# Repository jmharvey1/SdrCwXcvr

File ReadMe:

This repository contains files used to build the CW transceiver
shown in the YouTube Video at:
https://youtu.be/vxcRsNkiOTE
Some general instructions on how the files are to be used will be found here as well.
Use "SDR 74HC4052_Si5351R2_2020-03-30.zip" found in the Eagle/SDR 74HC4052 folder, to order a board from a pcb service, like JLCPCB.
Disclaimer: Some folders found here may not be complete. If you think that's preventing you
from being able to use them. Please use the "issues" section or the youtube's comments area 
to describe the problem. Hopefully I will be able to add the missing files.

Note: the "Quisk" folder supports Quisk running on Mint19.1 & Python 2.7. "quiskKW4KDpy3.tar.gz" is for Mint20 / Python 3. To install and run these versions of QUISK, follow the Linux Initial Installation" instuctions found here: 	https://james.ahlstrom.name/quisk/docs.html#Welcome
But use the source files found here, inplace of the onse referenced at the QUISK website

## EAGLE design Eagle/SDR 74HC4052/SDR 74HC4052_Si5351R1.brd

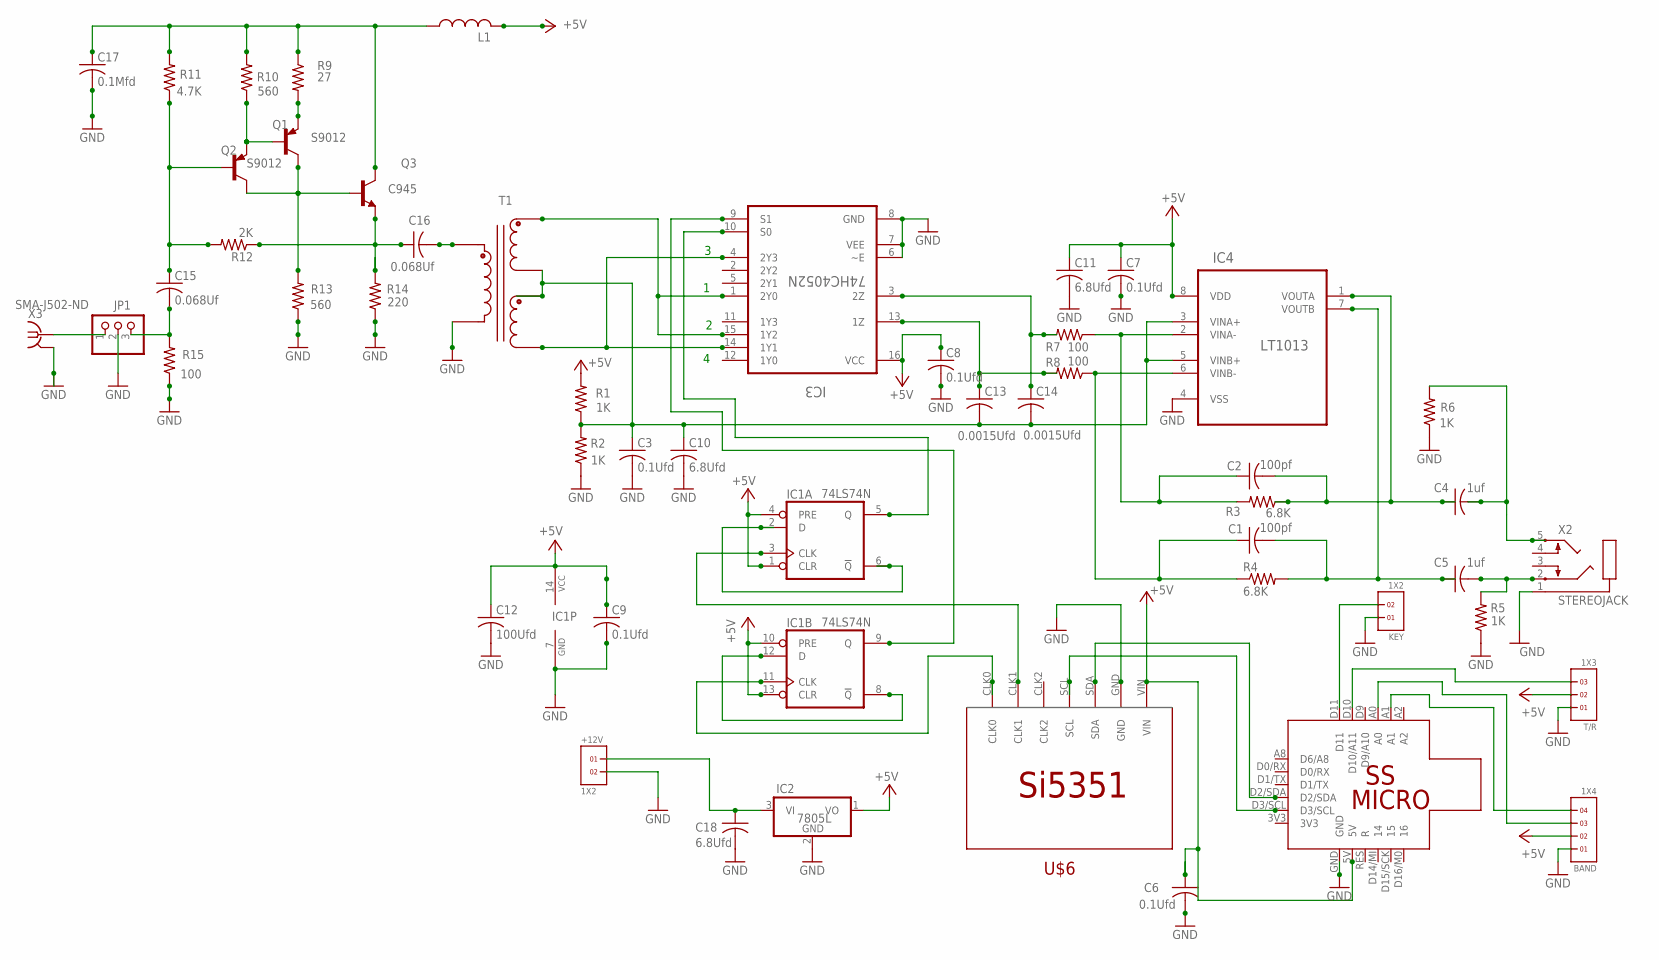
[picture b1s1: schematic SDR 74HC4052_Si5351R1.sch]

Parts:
+12V: 1X2
BAND: 1X4
C1, C2: 100pf; C050-024X044
C3, C6, C7, C8, C9: 0.1Ufd; C050-024X044
C4, C5: 1uf; C050-024X044
C10, C11, C18: 6.8Ufd; C050-024X044
C12: 100Ufd; C050-024X044
C13, C14: 0.0015Ufd; C050-024X044
C15, C16: 0.068Uf; C050-024X044
C17: 0.1Mfd; C050-024X044
IC1: 74LS74N; DIL14
IC2: 7805L; TO92
IC3: 74HC4052N; DIL16
IC4: LT1013; DIP254P762X533-8
JP1: PINHD-1X3CB; 1X03-CLEANBIG
KEY: 1X2
L1: L-US0207/12; 0207/12
Q1, Q2: S9012; TO92-CBE
Q3: C945; TO92-ECB
R1, R2, R5, R6: 1K; 0207/10
R3, R4: 6.8K; 0207/10
R7, R8: 100; 0207/10
R9: 27; 0207/7
R10, R13: 560; 0207/7
R11: 4.7K; 0207/7
R12: 2K; 0207/7
R14: 220; 0207/7
R15: 100; 0207/7
T1: T50_TRIFILAR_TRANSFORMER
T/R: 1X3
U$4: SS_MICRO
U$6: SI5351-BKBD; SI5351-BKOUT-BRD
X2: STEREOJACK; STX3100
X3: SMA-J502-ND; J502-ND

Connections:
+5V: BAND.2, C6.1, C7.1, C8.1, C9.1, C11.1, C12.1, IC1.1 (CLR), IC1.4 (PRE), IC1.10 (PRE), IC1.13 (CLR), IC1.14 (VCC), IC2.1 (VO), IC3.16 (VCC), IC4.8 (VDD), L1.2, R1.2, T/R.2, U$4.5V, U$6.VIN
GND: +12V.2, BAND.1, C3.2, C6.2, C7.2, C8.2, C9.2, C10.2, C11.2, C12.2, C17.2, C18.2, IC1.7 (GND), IC2.2 (GND), IC3.6 (~E), IC3.7 (VEE), IC3.8 (GND), IC4.4 (VSS), JP1.2, KEY.1, R2.1, R5.1, R6.1, R13.1, R14.1, R15.1, T1.C1A, T/R.1, U$4.GND, U$6.GND, X2.1, X3.2, X3.3 (2), X3.4 (2), X3.5 (2)
unnamed: C1.1, IC4.6 (VINB-), R4.1, R8.1
unnamed: C13.1, IC3.13 (1Z), R8.2
unnamed: C2.1, IC4.2 (VINA-), R3.2, R7.1
unnamed: C14.1, IC3.3 (2Z), R7.2
unnamed: C16.2, T1.C1B
unnamed: IC1.11 (CLK), U$6.CLK0
unnamed: IC1.5 (Q), IC3.10 (S0)
unnamed: IC3.1 (2Y0), IC3.15 (1Y2), T1.C2B
unnamed: C2.2, C4.1, IC4.1 (VOUTA), R3.1
unnamed: C1.2, C5.1, IC4.7 (VOUTB), R4.2
unnamed: Q1.E, R9.2
unnamed: U$4.D3/SCL, U$6.SCL
unnamed: U$4.D2/SDA, U$6.SDA
unnamed: C3.1, C10.1, C13.2, C14.2, IC4.3 (VINA+), IC4.5 (VINB+), R1.1, R2.2, T1.C2A, T1.C3B
unnamed: Q1.B, Q2.E, R10.1
unnamed: IC1.3 (CLK), U$6.CLK1
unnamed: IC3.4 (2Y3), IC3.14 (1Y1), T1.C3A
unnamed: IC1.9 (Q), IC3.9 (S1)
unnamed: C5.2, R5.2, X2.2
unnamed: C4.2, R6.2, X2.5
unnamed: IC1.2 (D), IC1.6 (!Q)
unnamed: IC1.8 (!Q), IC1.12 (D)
unnamed: Q1.C, Q2.C, Q3.B, R13.2
unnamed: C15.1, Q2.B, R11.1, R12.2
unnamed: C15.2, JP1.3, R15.2
unnamed: JP1.1, X3.1
unnamed: C16.1, Q3.E, R12.1, R14.2
unnamed: C17.1, L1.1, Q3.C, R9.1, R10.2, R11.2
unnamed: +12V.1, C18.1, IC2.3 (VI)
unnamed: T/R.3, U$4.D10 (D10/A11)
unnamed: BAND.3, U$4.A0
unnamed: BAND.4, U$4.A1
unnamed: KEY.2, U$4.D11

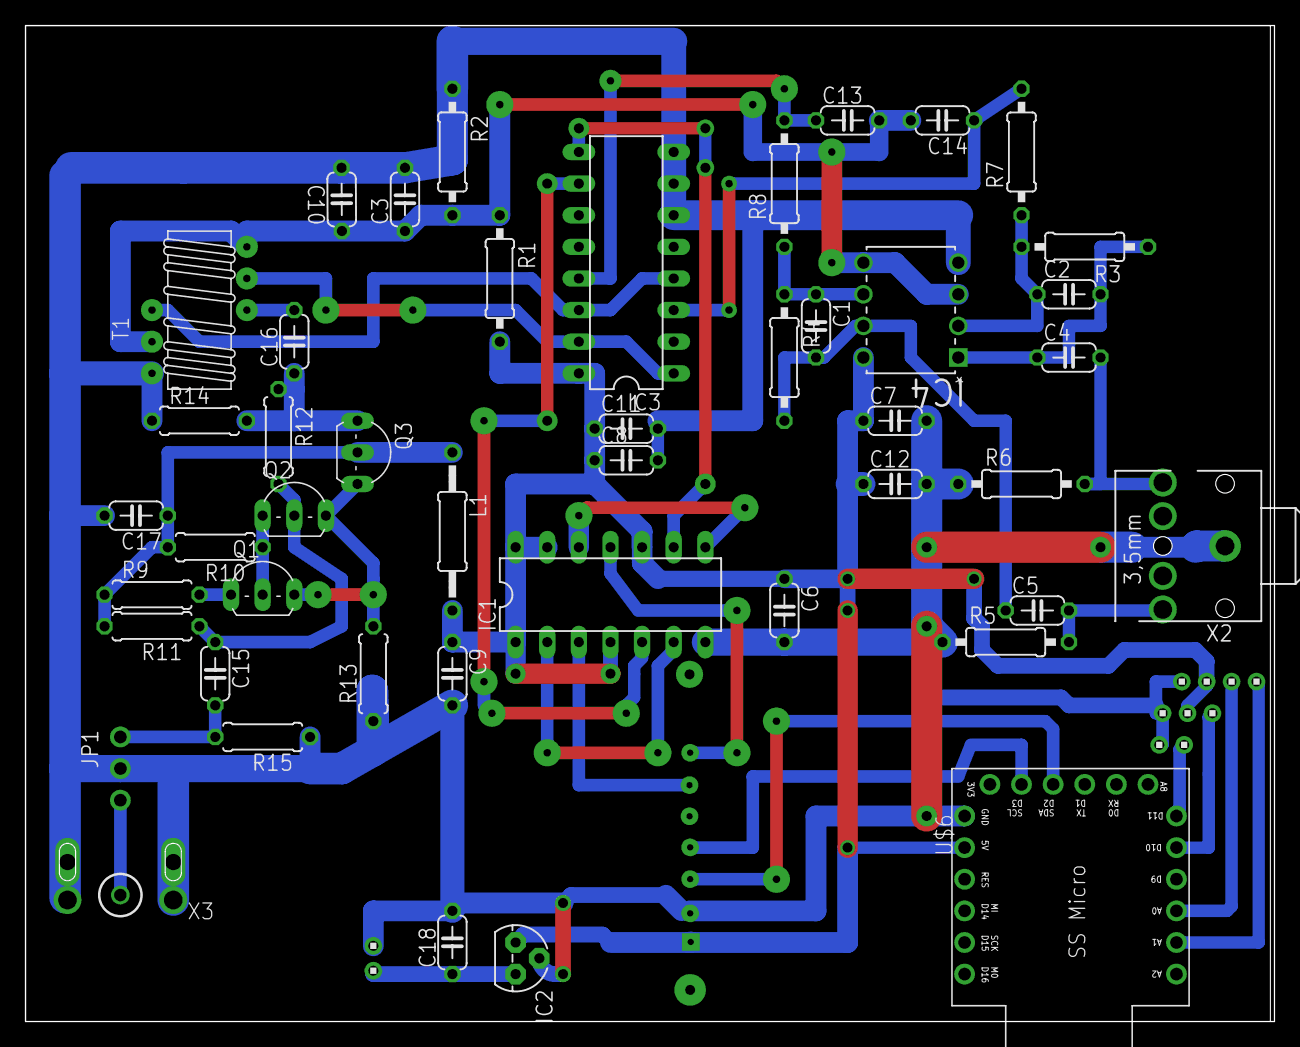
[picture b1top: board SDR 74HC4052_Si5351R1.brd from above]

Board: 2 copper layers, 100.3 x 80.0 mm, 51 parts (0 on the bottom side), 35 nets.

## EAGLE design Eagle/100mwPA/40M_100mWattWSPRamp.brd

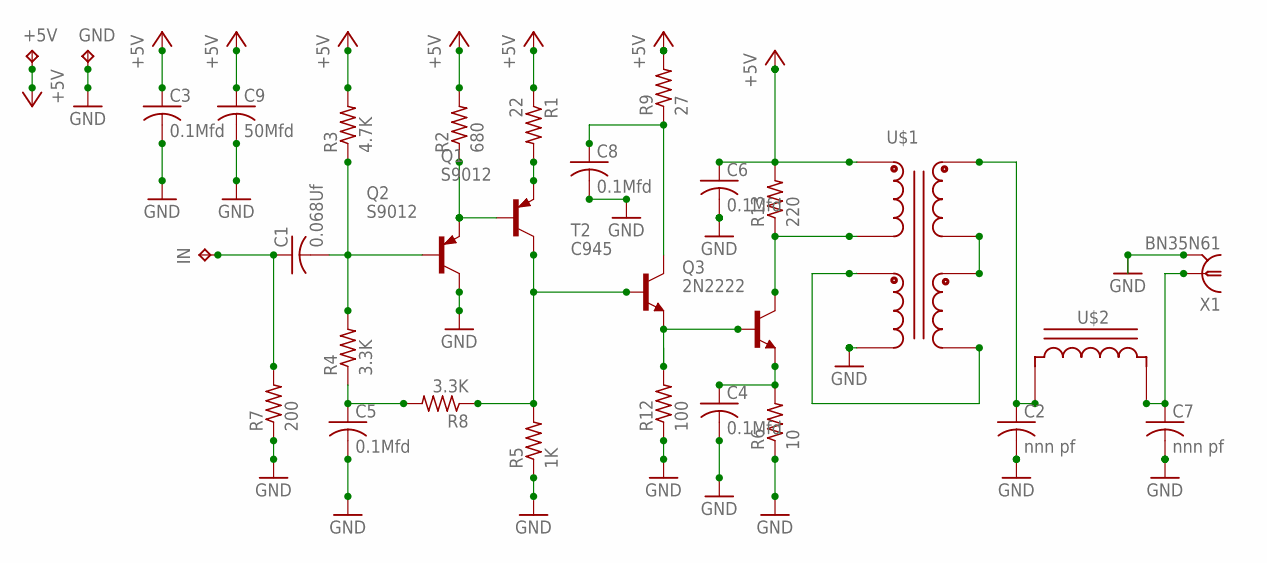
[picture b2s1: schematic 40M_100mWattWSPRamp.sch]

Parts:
+5V: TPPAD1-17Y; P1-17Y
C1: 0.068Uf; C050-024X044
C2, C7: nnn pf; C050-024X044
C3, C4, C5, C6, C8: 0.1Mfd; C050-024X044
C9: 50Mfd; C050-024X044
GND: TPPAD1-17Y; P1-17Y
IN: TPPAD1-17Y; P1-17Y
Q1, Q2: S9012; TO92-CBE
Q3: 2N2222; TO18
R1: 22; 0207/7
R2: 680; 0207/7
R3: 4.7K; 0207/7
R4, R8: 3.3K; 0207/7
R5: 1K; 0207/7
R6: 10; 0207/7
R7: 200; 0207/7
R9: 27; 0207/7
R12: 100; 0207/7
R13: 220; 0207/7
T2: C945; TO92-ECB
U$1: T50_QUADFILAR_TRANSFORMER
U$2: T50_INDUCTOR
X1: BN35N61; B35N61

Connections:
+5V: +5V.TP, C3.1, C6.1, C9.1, R1.1, R2.2, R3.2, R9.2, R13.2, U$1.C1B
+5V1: C5.1, R4.1, R8.2
+5V2: C2.1, U$1.C2B, U$2.CB
+5V3: C7.1, U$2.CA, X1.1
+5V4: C8.1, R9.1, T2.C
GND: C2.2, C3.2, C4.2, C5.2, C6.2, C7.2, C8.2, C9.2, GND.TP, Q2.C, R5.1, R6.1, R7.1, R12.1, U$1.C4A, X1.2, X1.3 (2), X1.4 (2), X1.5 (2)
unnamed: Q1.E, R1.2
unnamed: Q1.B, Q2.E, R2.1
unnamed: Q3.2 (B), R12.2, T2.E
unnamed: C1.2, Q2.B, R3.1, R4.2
unnamed: C1.1, IN.TP, R7.2
unnamed: U$1.C3A, U$1.C4B
unnamed: C4.1, Q3.1 (E), R6.2
unnamed: U$1.C2A, U$1.C3B
unnamed: Q1.C, R5.2, R8.1, T2.B
unnamed: Q3.3 (C), R13.1, U$1.C1A

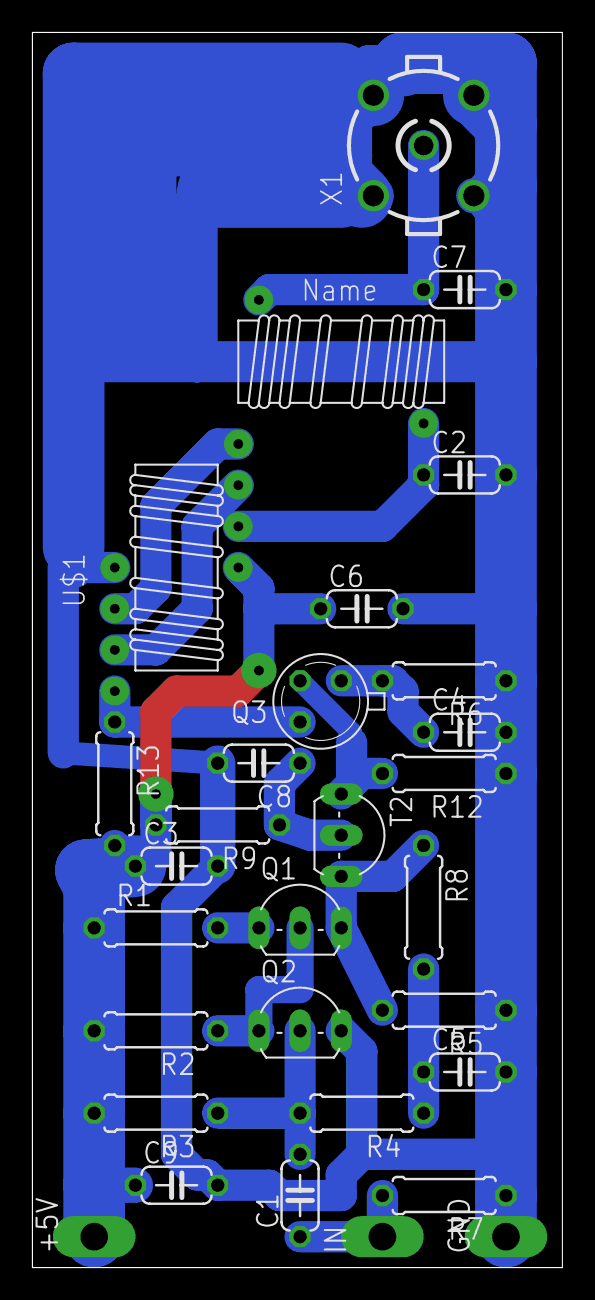
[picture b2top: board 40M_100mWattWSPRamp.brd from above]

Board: 2 copper layers, 32.7 x 76.2 mm, 30 parts (0 on the bottom side), 16 nets.

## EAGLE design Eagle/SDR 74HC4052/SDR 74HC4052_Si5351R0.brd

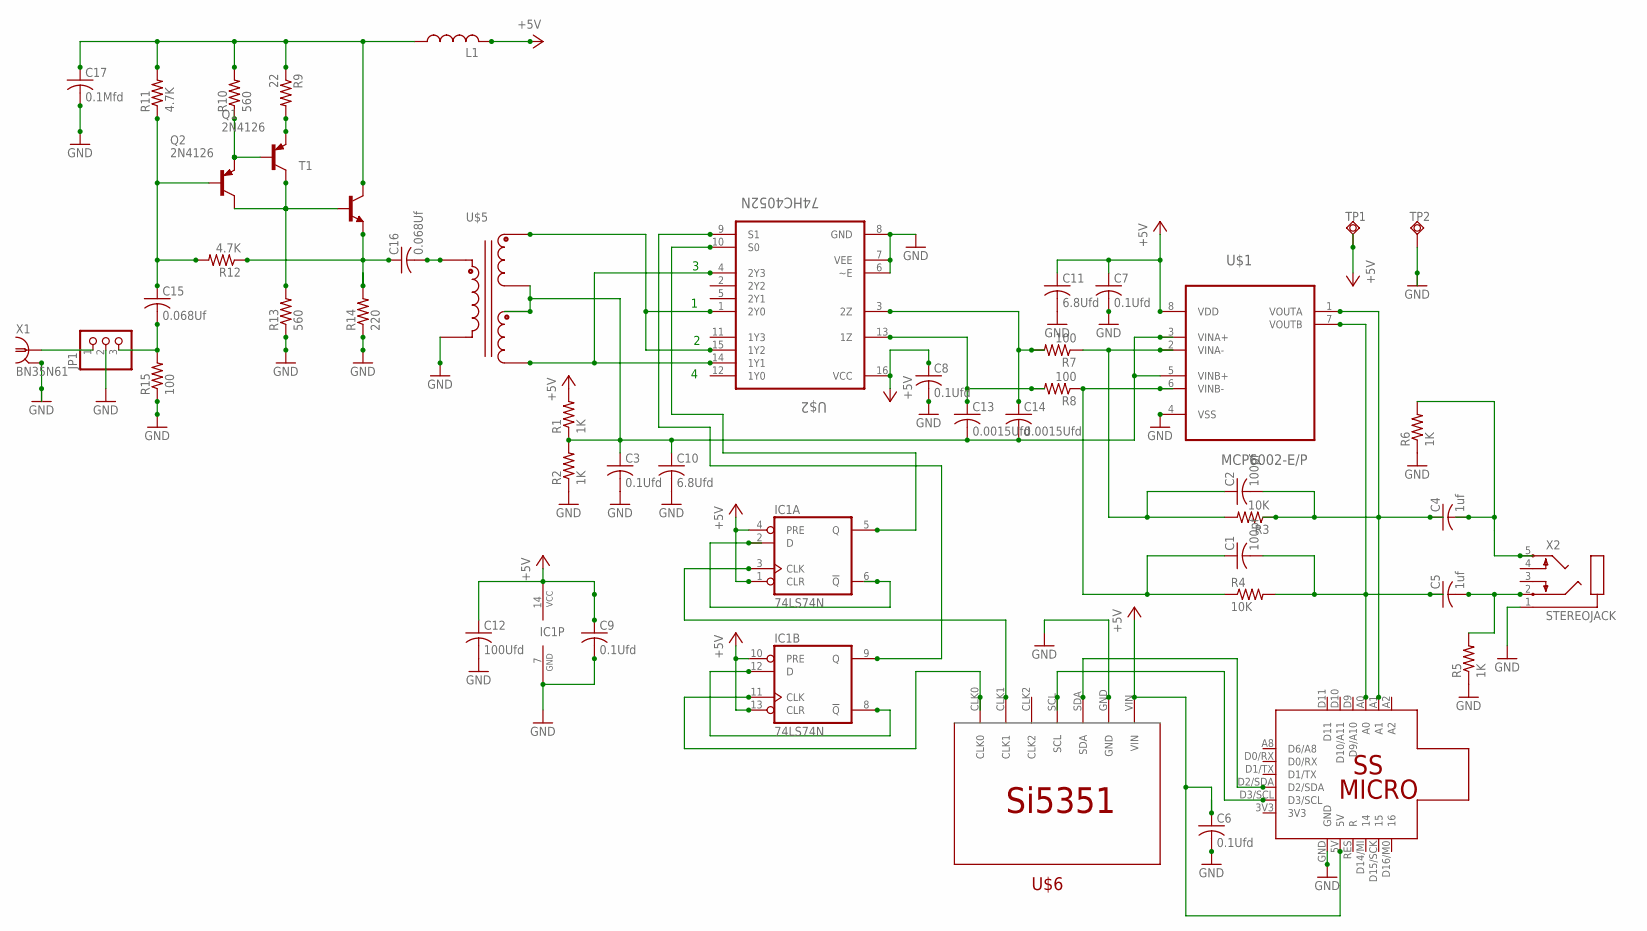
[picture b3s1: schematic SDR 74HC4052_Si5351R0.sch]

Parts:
C1, C2: 100pf; C050-024X044
C3, C6, C7, C8, C9: 0.1Ufd; C050-024X044
C4, C5: 1uf; C050-024X044
C10, C11: 6.8Ufd; C050-024X044
C12: 100Ufd; C050-024X044
C13, C14: 0.0015Ufd; C050-024X044
C15, C16: 0.068Uf; C050-024X044
C17: 0.1Mfd; C050-024X044
IC1: 74LS74N; DIL14
JP1: PINHD-1X3CB; 1X03-CLEANBIG
L1: L-US0207/12; 0207/12
Q1, Q2: 2N4126; TO92-CBE
R1, R2, R5, R6: 1K; 0207/10
R3, R4: 10K; 0207/10
R7, R8: 100; 0207/10
R9: 22; 0207/7
R10, R13: 560; 0207/7
R11, R12: 4.7K; 0207/7
R14: 220; 0207/7
R15: 100; 0207/7
T1: -NPN-TO92-ECB; TO92-ECB
TP1, TP2: TPSQPAD1-20Y; P1-20Y
U$1: MCP6002-E/P; DIP254P762X533-8
U$2: 74HC4052N; DIL16
U$4: SS_MICRO
U$5: T50_TRIFILAR_TRANSFORMER
U$6: SI5351-BKBD; SI5351-BKOUT-BRD
X1: BN35N61; B35N61
X2: STEREOJACK; STX3100

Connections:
+5V: C6.1, C7.1, C8.1, C9.1, C11.1, C12.1, IC1.1 (CLR), IC1.4 (PRE), IC1.10 (PRE), IC1.13 (CLR), IC1.14 (VCC), L1.2, R1.2, TP1.TP, U$1.8 (VDD), U$2.16 (VCC), U$4.5V, U$6.VIN
GND: C3.2, C6.2, C7.2, C8.2, C9.2, C10.2, C11.2, C12.2, C17.2, IC1.7 (GND), JP1.2, R2.1, R5.1, R6.1, R13.1, R14.1, R15.1, TP2.TP, U$1.4 (VSS), U$2.6 (~E), U$2.7 (VEE), U$2.8 (GND), U$4.GND, U$5.C1A, U$6.GND, X1.2, X1.3 (2), X1.4 (2), X1.5 (2), X2.1
unnamed: C1.1, R4.1, R8.1, U$1.6 (VINB-)
unnamed: C13.1, R8.2, U$2.13 (1Z)
unnamed: C2.1, R3.2, R7.1, U$1.2 (VINA-)
unnamed: C14.1, R7.2, U$2.3 (2Z)
unnamed: C16.2, U$5.C1B
unnamed: IC1.11 (CLK), U$6.CLK0
unnamed: IC1.5 (Q), U$2.10 (S0)
unnamed: U$2.1 (2Y0), U$2.15 (1Y2), U$5.C2B
unnamed: C2.2, C4.1, R3.1, U$1.1 (VOUTA), U$4.A1
unnamed: C1.2, C5.1, R4.2, U$1.7 (VOUTB), U$4.A0
unnamed: Q1.E, R9.2
unnamed: U$4.D3/SCL, U$6.SCL
unnamed: U$4.D2/SDA, U$6.SDA
unnamed: C3.1, C10.1, C13.2, C14.2, R1.1, R2.2, U$1.3 (VINA+), U$1.5 (VINB+), U$5.C2A, U$5.C3B
unnamed: Q1.B, Q2.E, R10.1
unnamed: IC1.3 (CLK), U$6.CLK1
unnamed: U$2.4 (2Y3), U$2.14 (1Y1), U$5.C3A
unnamed: IC1.9 (Q), U$2.9 (S1)
unnamed: C5.2, R5.2, X2.2
unnamed: C4.2, R6.2, X2.5
unnamed: IC1.2 (D), IC1.6 (!Q)
unnamed: IC1.8 (!Q), IC1.12 (D)
unnamed: Q1.C, Q2.C, R13.2, T1.B
unnamed: C15.1, Q2.B, R11.1, R12.2
unnamed: C15.2, JP1.3, R15.2
unnamed: JP1.1, X1.1
unnamed: C16.1, R12.1, R14.2, T1.E
unnamed: C17.1, L1.1, R9.1, R10.2, R11.2, T1.C

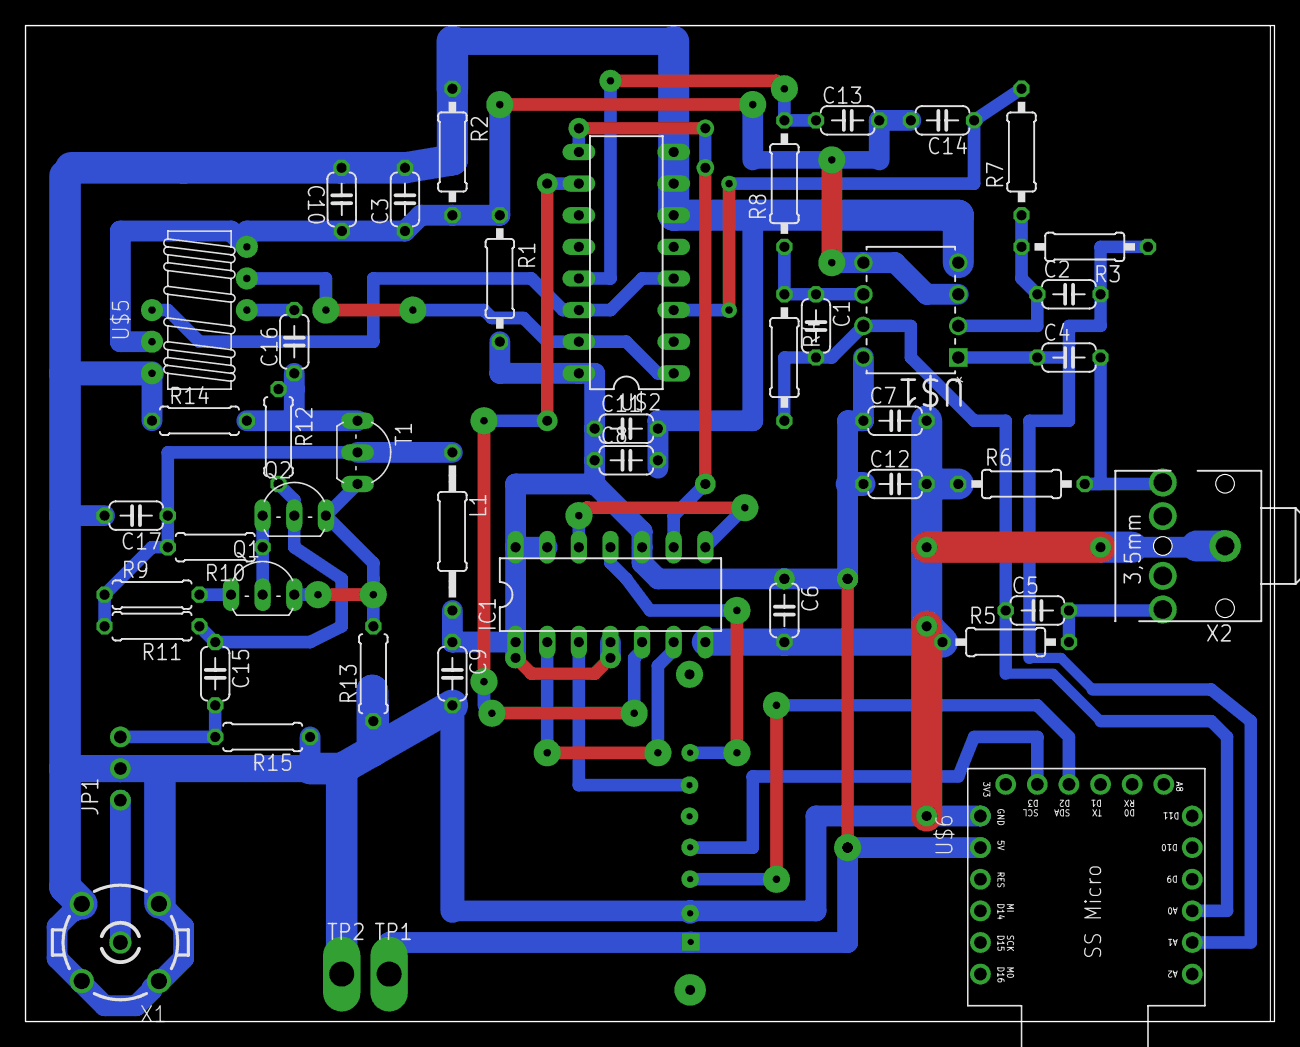
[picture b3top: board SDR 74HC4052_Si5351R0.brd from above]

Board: 2 copper layers, 100.3 x 80.0 mm, 47 parts (0 on the bottom side), 30 nets.

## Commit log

2018-12-14 Initial file upload
    1st upload
2018-12-14 Part of initial push
    Python QUISK files with mods to be compliant with SDR CW Xcvr project
2018-12-15 Add 100mw pa eagle files
    5 volt 100 mw pa using discrete transistors and through hole
    consturction; A companion xmt brd for the SDR CW Xcvr project
2018-12-18 Update ReadMe
    added youtube hyper link & disclaimer to ReadMe file
2019-01-07 new dual screen version of QUISK
2019-01-07 moved latest version of quisk to quisk folder
    This version of quisk uses two screens to better utlize desktop space
2019-01-08 add FLDIGI files
    This version of FLDIGI supports Streaming Key commands via usb and Auto
    CW Xmt
2019-01-08 Updated FLDIGI to support Logbook pushes ot QRZ
    User needs to enter their logbook API Key Id in QRZlogbook.cxx to
    enable this feature
2019-04-18 Update project related files
    Updating project files to mirror the current configuration of the SDR
2019-08-05 Added Quisk for Mint19.1
    reworked quisk files to be compatible python and related resources found
    on Linux Mint19.1
2019-08-06 Files needed to build _quisk.so
    added just the files needed to build the current version of _quisk.so
2019-08-19 Updated QUISK files
    Added install Notes and Updated QUISK program files to QUISK4.1.41
    fteatures plus minor enhancements to the KW4KD features
2019-08-27 updated Quisk files
    cleaned up debug talk
2019-09-06 Added FLDIGI compiled for LinuxMint19.1
    Added FLDIGI compiled for LinuxMint19.1
2019-09-15 enhanced support for external manul keying
    Revised both QUISK files and SSmicro sketch to better support the use of
    an external key to send CW
2020-06-10 Resynced Files to represent latest configuration
    Resynced Files to represent latest configuration
2020-09-18 New version of FLDIGI.exe to better support QSK
    The FLDIGI executable is intended for windows users, who want to operat
    semi QSK (CW) on rigs other than the QUISK based SDR Xcvr used in this
    project
2020-11-25 Added Python 3 comaptible version of stock QUISK app
    files were "compressed" to save space
2020-12-02 Added Mint20 Python 3.x Quisk/KW4KD source file
    First beta version of Mint20 QUISK
2020-12-06 QUISK Python3/Mint20 code tweaks
    QUISK Python3/Mint20
    code changes to cleanup application shutdown processes
2020-12-08 fixed potential startup/initialization issue with mint20 version of QUISK
    Forced save of quisk_init.json file on shutdown to insure a previously
    corrupted copy gets replaced
2020-12-12 Cleaned up FLDIGI Folder
    Updated FLDIGI sound code
2020-12-13 More tweaks to FLDIGI code
    these code changes further reduce background process switching during CW
    TX periods
2021-01-03 step change 1
2021-01-03 step change 2
2021-01-03 step change 3
    Added updated SS Micro sketch back to repository
2021-01-03 Added Quisk source files back to repository
    Collective changes made today revise the methods used to steam keying
    data from FLDIGI to the Arduino SSmicro thruogh QUISK. this updates
    FLDIGI to conform to the standards/techniques employed in version 4.1.17
2021-01-28 Updated FLDIGI files
    Minor changes to FLDIGI to conform to new key streaming protocol
2021-01-28 Added Latest Quisk Files
    Added Latest Quisk Files
2021-01-30 Fixed SSMicro Sketch to handle FLDIGI "TUNE" stream
    FLDIGI Tune stream ended with keydown command. This left old ss micro
    sketch in an indeterment state. At times leaving the T/R in the TX state
    and could also leave QUISK hung in "send/tx" mode. This small change
    ensures that both QUISK and the T/R control lead are set to receive when
    the key steaming stops
2021-02-04 Revised code to support Gen2 Keystream
    This Update changes how the Key stream is processed. The majority of the
    change is contained in the SSMicro Sketch. It adapts the element timing
    to maintain a more or less constant buffer depth. Also used is a speed
    table allowing each speed (5 to 35 WPM) to have custom parameters
2021-02-04 Minor tweak to FLDIGI to support GEN2 keying
    Found FLDIGI was sending an "extra" PTT command, that is not needed with
    Gen2 signaling
2021-11-13 Change to SSMicro Sketch to fix timeout issue when Manually Keying the Transmitter
    Added "if" condition to block "streaming timeout" from forcing the SDR
    in to receive mode while being manually keyed
2024-12-06 Added SDR 74HC4052_Si5351R2_2020-03-30.zip for PCB service support
2024-12-06 ReadMe updated path to SDR 74HC4052_Si5351R2_2020-03-30.zip
